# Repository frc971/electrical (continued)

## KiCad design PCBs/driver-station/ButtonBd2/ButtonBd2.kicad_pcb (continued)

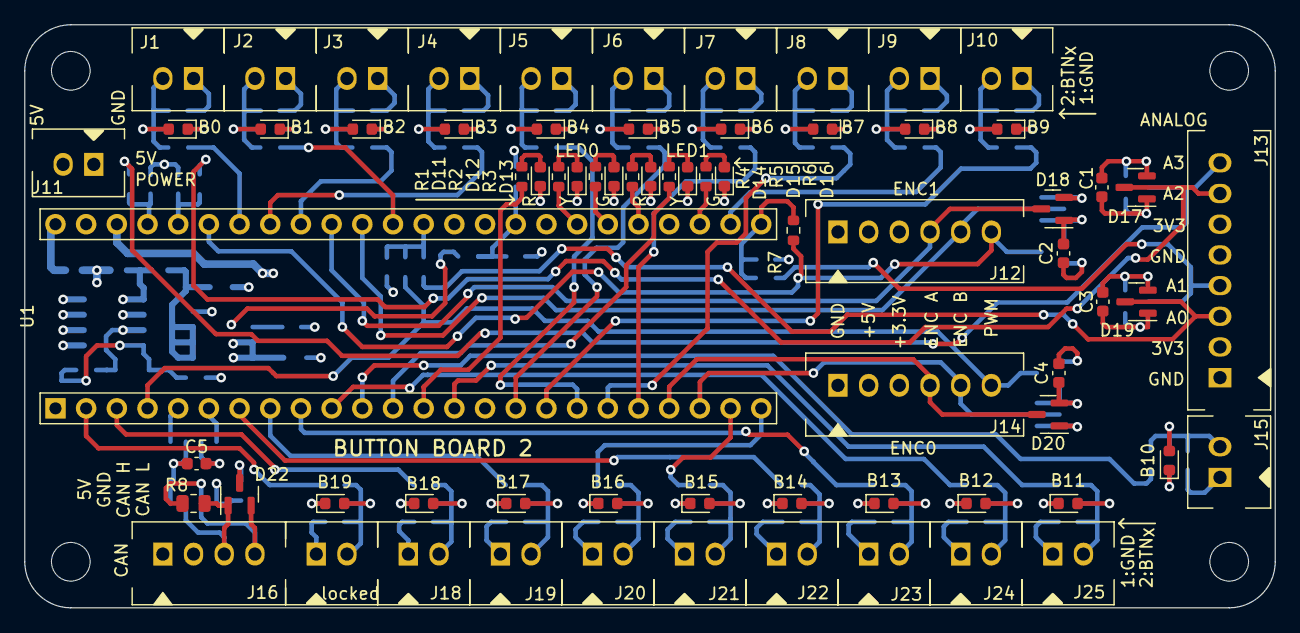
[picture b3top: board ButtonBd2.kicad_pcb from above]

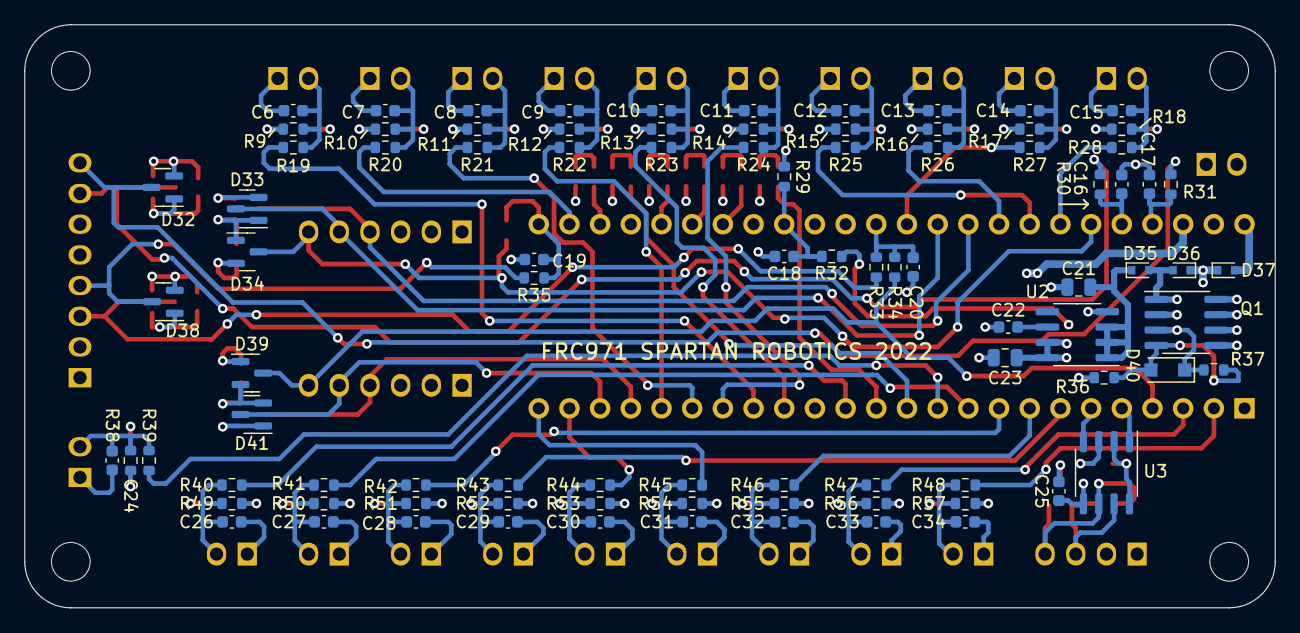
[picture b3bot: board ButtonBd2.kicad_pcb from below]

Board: 4 copper layers, 103.5 x 48.3 mm, 165 parts (91 on the bottom side), 100 nets.

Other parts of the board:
locked: B19; 70543-0001

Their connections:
/Button Inputs/BN19: locked.2; also elsewhere on the board
GND: locked.1; also elsewhere on the board

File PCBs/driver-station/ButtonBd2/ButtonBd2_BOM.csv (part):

Source:,/home/scott/Documents/Projects/FRC/ButtonBoard2/ButtonBd2/ButtonBd2.kicad_sch,,,,,,,
Date:,Sun 18 Dec 2022 03:10:28 PM PST,,,,,,,
Tool:,Eeschema 6.0.7-f9a2dced07~116~ubuntu20.04.1,,,,,,,
Generator:,/usr/share/kicad/plugins/bom_csv_grouped_by_value.py,,,,,,,
Component Count:,161,,,,,,,
,,,,,,,,
,,,,,,,,
Item,Qty,Reference(s),Value,LibPart,Footprint,Datasheet,MFG,MFG P/N
1,11,"C1, C2, C3, C4, C5, C16, C17, C18, C19, C20, C25",0.1uF-10%-50V-0603,Device:C,Capacitor_SMD:C_0603_1608Metric,~,Samsung Electro-Mechanics,CL10B104KB8NNNC
2,20,"C6, C7, C8, C9, C10, C11, C12, C13, C14, C15, C24, C26, C27, C28, C29, C30, C31, C32, C33, C34",1nF-50V-10%-0603,Device:C,Capacitor_SMD:C_0603_1608Metric,~,Samsung Electro-Mechanics,CL10B102KB8NNNC
3,1,C21,22uF-10V-10%-0805,Device:C,Capacitor_SMD:C_0805_2012Metric,~,Samsung Electro-Mechanics,CL21A226KPCLRNC
4,1,C22,3.3nF-50V-10%-0603,Device:C,Capacitor_SMD:C_0603_1608Metric,~,Samsung Electro-Mechanics,CL10B332KB8NNNC
5,1,C23,1uF-25V-10%-0805,Device:C,Capacitor_SMD:C_0805_2012Metric,~,Samsung Electro-Mechanics,CL21B105KAFNNNE
6,1,D1,BTN0,Device:LED,LED_SMD:LED_0603_1608Metric,https://www.we-online.com/katalog/datasheet/150060YS75000.pdf,Wurth Electronik,150060YS75000
7,1,D2,BTN1,Device:LED,LED_SMD:LED_0603_1608Metric,https://www.we-online.com/katalog/datasheet/150060YS75000.pdf,Wurth Electronik,150060YS75000
8,1,D3,BTN2,Device:LED,LED_SMD:LED_0603_1608Metric,https://www.we-online.com/katalog/datasheet/150060YS75000.pdf,Wurth Electronik,150060YS75000
9,1,D4,BTN3,Device:LED,LED_SMD:LED_0603_1608Metric,https://www.we-online.com/katalog/datasheet/150060YS75000.pdf,Wurth Electronik,150060YS75000
10,1,D5,BTN4,Device:LED,LED_SMD:LED_0603_1608Metric,https://www.we-online.com/katalog/datasheet/150060YS75000.pdf,Wurth Electronik,150060YS75000
11,1,D6,BTN5,Device:LED,LED_SMD:LED_0603_1608Metric,https://www.we-online.com/katalog/datasheet/150060YS75000.pdf,Wurth Electronik,150060YS75000
12,1,D7,BTN6,Device:LED,LED_SMD:LED_0603_1608Metric,https://www.we-online.com/katalog/datasheet/150060YS75000.pdf,Wurth Electronik,150060YS75000
13,1,D8,BTN7,Device:LED,LED_SMD:LED_0603_1608Metric,https://www.we-online.com/katalog/datasheet/150060YS75000.pdf,Wurth Electronik,150060YS75000
14,1,D9,BTN8,Device:LED,LED_SMD:LED_0603_1608Metric,https://www.we-online.com/katalog/datasheet/150060YS75000.pdf,Wurth Electronik,150060YS75000
15,1,D10,BTN9,Device:LED,LED_SMD:LED_0603_1608Metric,https://www.we-online.com/katalog/datasheet/150060YS75000.pdf,Wurth Electronik,150060YS75000
16,1,D11,0R,Device:LED,LED_SMD:LED_0603_1608Metric,http://www.stanley-components.com/php/downloaddatafile.php?r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,Stanley Electric,BR1111C-TR
17,1,D12,0Y,Device:LED,LED_SMD:LED_0603_1608Metric,https://www.we-online.com/katalog/datasheet/150060YS75000.pdf,Wurth Electronik,150060YS75000
18,1,D13,0G,Device:LED,LED_SMD:LED_0603_1608Metric,https://www.we-online.com/katalog/datasheet/150060YS75000.pdf,Wurth Electronik,150060GS75000
19,1,D14,1R,Device:LED,LED_SMD:LED_0603_1608Metric,http://www.stanley-components.com/php/downloaddatafile.php?r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,Stanley Electric,BR1111C-TR
20,1,D15,1Y,Device:LED,LED_SMD:LED_0603_1608Metric,https://www.we-online.com/katalog/datasheet/150060YS75000.pdf,Wurth Electronik,150060YS75000
21,1,D16,1G,Device:LED,LED_SMD:LED_0603_1608Metric,https://www.we-online.com/katalog/datasheet/150060YS75000.pdf,Wurth Electronik,150060GS75000
22,10,"D17, D18, D19, D20, D32, D33, D34, D38, D39, D41",BAV99,Diode:BAV99,Package_TO_SOT_SMD:SOT-23,https://assets.nexperia.com/documents/data-sheet/BAV99_SER.pdf,Nexperia USA Inc.,"BAV99,235"
23,1,D21,BTN10,Device:LED,LED_SMD:LED_0603_1608Metric,https://www.we-online.com/katalog/datasheet/150060YS75000.pdf,Wurth Electronik,150060YS75000
24,1,D22,PESD1CAN,PI-Power-Board:PESD1CAN,Package_TO_SOT_SMD:SOT-23,https://assets.nexperia.com/documents/data-sheet/PESD1CAN.pdf,Nexperia,"PESD1CAN,215"
25,1,D23,BTN19,Device:LED,LED_SMD:LED_0603_1608Metric,https://www.we-online.com/katalog/datasheet/150060YS75000.pdf,Wurth Electronik,150060YS75000
26,1,D24,BTN18,Device:LED,LED_SMD:LED_0603_1608Metric,https://www.we-online.com/katalog/datasheet/150060YS75000.pdf,Wurth Electronik,150060YS75000
27,1,D25,BTN17,Device:LED,LED_SMD:LED_0603_1608Metric,https://www.we-online.com/katalog/datasheet/150060YS75000.pdf,Wurth Electronik,150060YS75000
28,1,D26,BTN16,Device:LED,LED_SMD:LED_0603_1608Metric,https://www.we-online.com/katalog/datasheet/150060YS75000.pdf,Wurth Electronik,150060YS75000
29,1,D27,BTN15,Device:LED,LED_SMD:LED_0603_1608Metric,https://www.we-online.com/katalog/datasheet/150060YS75000.pdf,Wurth Electronik,150060YS75000
30,1,D28,BTN14,Device:LED,LED_SMD:LED_0603_1608Metric,https://www.we-online.com/katalog/datasheet/150060YS75000.pdf,Wurth Electronik,150060YS75000
31,1,D29,BTN13,Device:LED,LED_SMD:LED_0603_1608Metric,https://www.we-online.com/katalog/datasheet/150060YS75000.pdf,Wurth Electronik,150060YS75000
32,1,D30,BTN12,Device:LED,LED_SMD:LED_0603_1608Metric,https://www.we-online.com/katalog/datasheet/150060YS75000.pdf,Wurth Electronik,150060YS75000
33,1,D31,BTN11,Device:LED,LED_SMD:LED_0603_1608Metric,https://www.we-online.com/katalog/datasheet/150060YS75000.pdf,Wurth Electronik,150060YS75000
34,3,"D35, D36, D37",NSR05T40XV2T5G,Device:D_Schottky,Diode_SMD:D_SOD-523,~,onsemi,NSR05T40XV2T5G
35,1,D40,15V,Device:D_Zener,Diode_SMD:D_SOD-123F,~,Nexperia,"BZT52H-C15,115"
36,1,J1,B0,Connector:Conn_01x02_Male,ButtonBd2:70543-0001,https://www.molex.com/pdm_docs/sd/705430001_sd.pdf,Molex,70541-0001
37,1,J2,B1,Connector:Conn_01x02_Male,ButtonBd2:70543-0001,https://www.molex.com/pdm_docs/sd/705430001_sd.pdf,Molex,70541-0001
38,1,J3,B2,Connector:Conn_01x02_Male,ButtonBd2:70543-0001,https://www.molex.com/pdm_docs/sd/705430001_sd.pdf,Molex,70541-0001
39,1,J4,B3,Connector:Conn_01x02_Male,ButtonBd2:70543-0001,https://www.molex.com/pdm_docs/sd/705430001_sd.pdf,Molex,70541-0001
40,1,J5,B4,Connector:Conn_01x02_Male,ButtonBd2:70543-0001,https://www.molex.com/pdm_docs/sd/705430001_sd.pdf,Molex,70541-0001
41,1,J6,B5,Connector:Conn_01x02_Male,ButtonBd2:70543-0001,https://www.molex.com/pdm_docs/sd/705430001_sd.pdf,Molex,70541-0001
42,1,J7,B6,Connector:Conn_01x02_Male,ButtonBd2:70543-0001,https://www.molex.com/pdm_docs/sd/705430001_sd.pdf,Molex,70541-0001
43,1,J8,B7,Connector:Conn_01x02_Male,ButtonBd2:70543-0001,https://www.molex.com/pdm_docs/sd/705430001_sd.pdf,Molex,70541-0001
44,1,J9,B8,Connector:Conn_01x02_Male,ButtonBd2:70543-0001,https://www.molex.com/pdm_docs/sd/705430001_sd.pdf,Molex,70541-0001
45,1,J10,B9,Connector:Conn_01x02_Male,ButtonBd2:70543-0001,https://www.molex.com/pdm_docs/sd/705430001_sd.pdf,Molex,70541-0001
46,1,J11,POWER,Connector:Conn_01x02_Male,ButtonBd2:70543-0001,https://www.molex.com/pdm_docs/sd/705430001_sd.pdf,Molex,70541-0001
47,1,J12,ENC1,Connector:Conn_01x06_Male,ButtonBd2:70543-0005,https://www.molex.com/pdm_docs/sd/705430001_sd.pdf,Molex,70541-0005
48,1,J13,ANALOG,Connector:Conn_01x08_Male,ButtonBd2:70543-0007,https://www.molex.com/pdm_docs/sd/705430001_sd.pdf,Molex,70541-0007
49,1,J14,ENC0,Connector:Conn_01x06_Male,ButtonBd2:70543-0005,https://www.molex.com/pdm_docs/sd/705430001_sd.pdf,Molex,70541-0005
50,1,J15,B10,Connector:Conn_01x02_Male,ButtonBd2:70543-0001,https://www.molex.com/pdm_docs/sd/705430001_sd.pdf,Molex,70541-0001
51,1,J16,CAN,Connector:Conn_01x04_Male,ButtonBd2:70543-0003,https://www.molex.com/pdm_docs/sd/705430001_sd.pdf,Molex,70541-0003
52,1,J17,B19,Connector:Conn_01x02_Male,ButtonBd2:70543-0001,https://www.molex.com/pdm_docs/sd/705430001_sd.pdf,Molex,70541-0001
53,1,J18,B18,Connector:Conn_01x02_Male,ButtonBd2:70543-0001,https://www.molex.com/pdm_docs/sd/705430001_sd.pdf,Molex,70541-0001
54,1,J19,B17,Connector:Conn_01x02_Male,ButtonBd2:70543-0001,https://www.molex.com/pdm_docs/sd/705430001_sd.pdf,Molex,70541-0001
55,1,J20,B16,Connector:Conn_01x02_Male,ButtonBd2:70543-0001,https://www.molex.com/pdm_docs/sd/705430001_sd.pdf,Molex,70541-0001
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
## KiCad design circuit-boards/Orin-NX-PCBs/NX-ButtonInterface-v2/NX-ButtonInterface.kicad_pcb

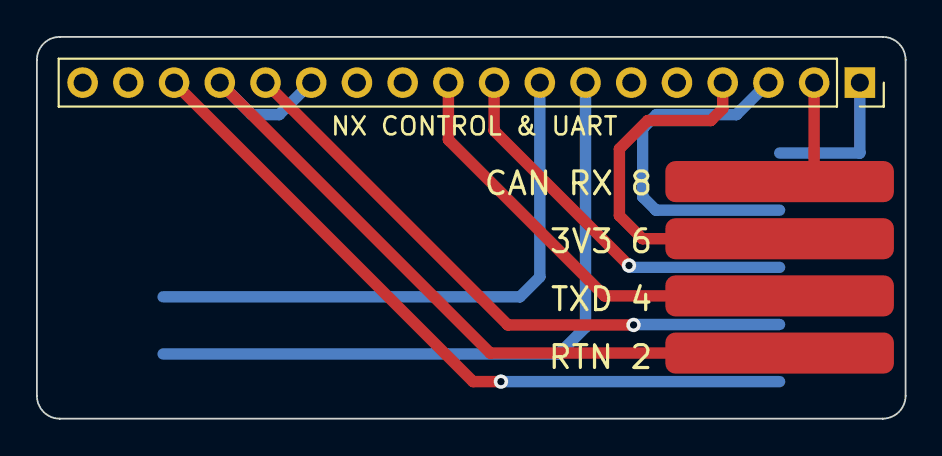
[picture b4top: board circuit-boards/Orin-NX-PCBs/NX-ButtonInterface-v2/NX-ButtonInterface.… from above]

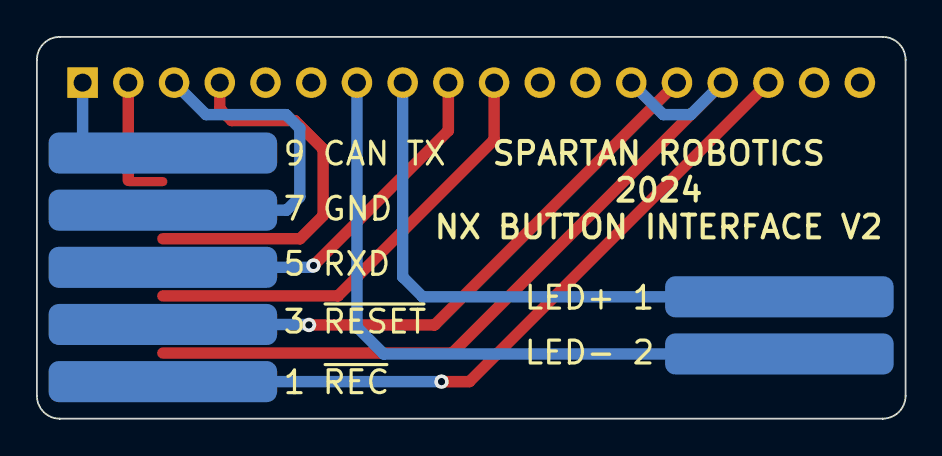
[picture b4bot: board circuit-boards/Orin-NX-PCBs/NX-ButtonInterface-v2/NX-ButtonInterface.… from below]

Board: 2 copper layers, 48.3 x 21.2 mm, 3 parts (2 on the bottom side), 11 nets.

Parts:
J1: NX CONTROL & UART; PinSocket_1x18_P2.54mm_Vertical
J2: NX-BUTTON; 9-pin-solder-pads
J4: POWER LED; 2-pin-solder-pads

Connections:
/3V3: J1.4, J2.6
/CAN_RX: J1.2, J2.8
/CAN_TX: J1.1, J2.9
/GND: J1.3, J2.7
/NX_PC_LED+: J1.8, J4.1
/NX_PC_LED-: J1.7, J4.2
/SYS_RST_RCV_RTN: J1.13, J1.15, J2.2
/UART2_RXD: J1.9, J2.5
/UART2_TXD: J1.10, J2.4
/~REC: J1.16, J2.1
/~SYS_RESET: J1.14, J2.3

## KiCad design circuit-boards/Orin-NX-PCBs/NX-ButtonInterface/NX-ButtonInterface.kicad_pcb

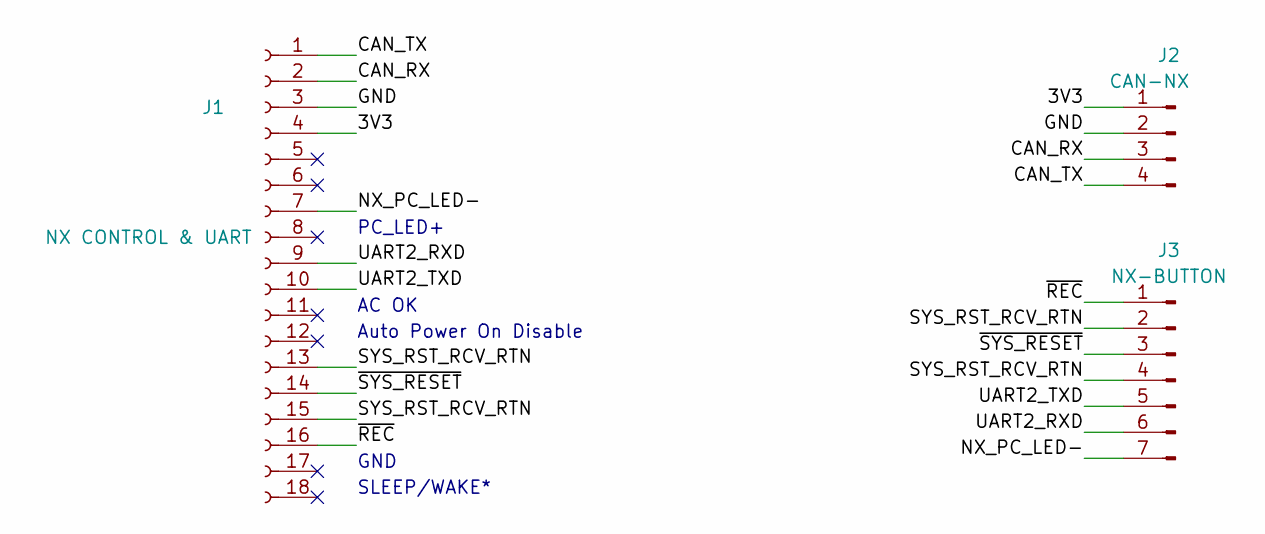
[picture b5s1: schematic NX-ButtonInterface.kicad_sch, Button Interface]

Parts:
J1: NX CONTROL & UART; PinSocket_1x18_P2.54mm_Vertical; MFG P/N PPTC181LFBN-RC
J2: CAN-NX; 4-pin-solder-pads
J3: NX-BUTTON; 7-pin-solder-pads

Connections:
/3V3: J1.4, J2.1
/CAN_RX: J1.2, J2.3
/CAN_TX: J1.1, J2.4
/GND: J1.3, J2.2
/NX_PC_LED-: J1.7, J3.7
/SYS_RST_RCV_RTN: J1.13, J1.15, J3.2, J3.4
/UART2_RXD: J1.9, J3.6
/UART2_TXD: J1.10, J3.5
/~REC: J1.16, J3.1
/~SYS_RESET: J1.14, J3.3

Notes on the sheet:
AC OK
GND
PC_LED+
Auto Power On Disable
SLEEP/WAKE*

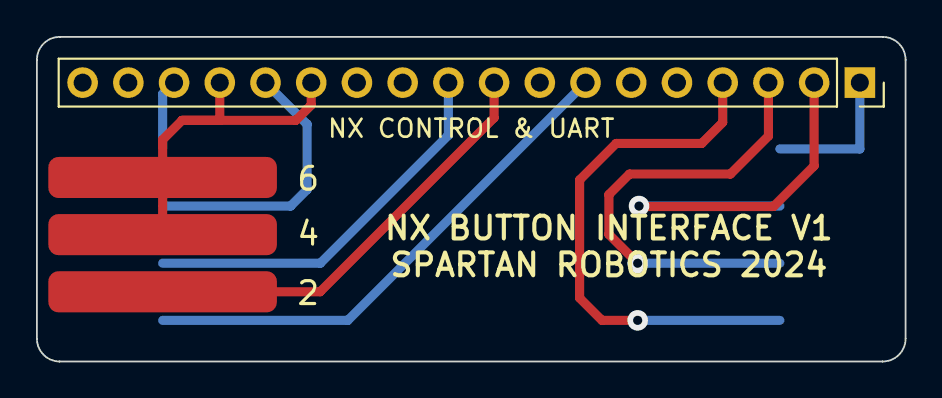
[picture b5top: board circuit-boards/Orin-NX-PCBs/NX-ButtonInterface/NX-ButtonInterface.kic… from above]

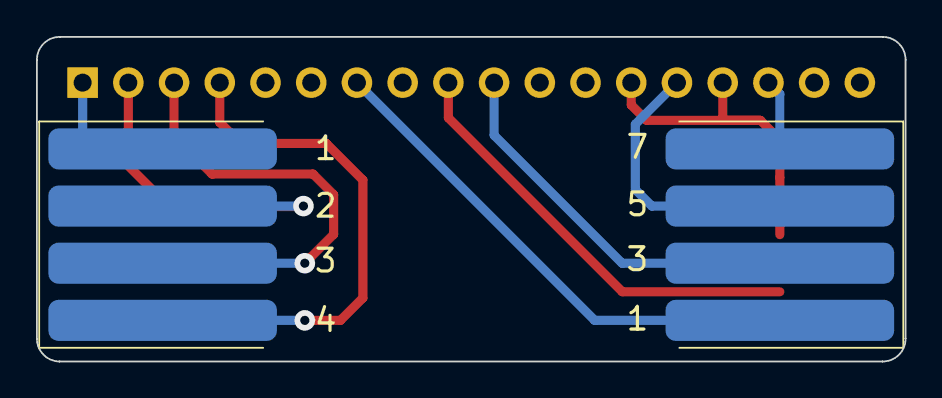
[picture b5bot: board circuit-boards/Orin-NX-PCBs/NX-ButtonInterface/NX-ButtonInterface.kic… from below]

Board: 2 copper layers, 48.3 x 18.0 mm, 3 parts (2 on the bottom side), 10 nets.

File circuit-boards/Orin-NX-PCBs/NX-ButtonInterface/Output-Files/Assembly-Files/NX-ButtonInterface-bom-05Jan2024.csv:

Item, Qty, Reference(s), Value, DIST, DIST P/N, MFG, MFG P/N, 
"1","1","J1","NX CONTROL & UART","Digikey","S7016-ND","Sullins Connector Solutions","PPTC181LFBN-RC"
"2","1","J2","CAN-NX","Digikey","WM4802-ND","Molex","0705430003"
"3","1","J3","NX-BUTTON","Digikey","WM4805-ND","Molex","0705430006"

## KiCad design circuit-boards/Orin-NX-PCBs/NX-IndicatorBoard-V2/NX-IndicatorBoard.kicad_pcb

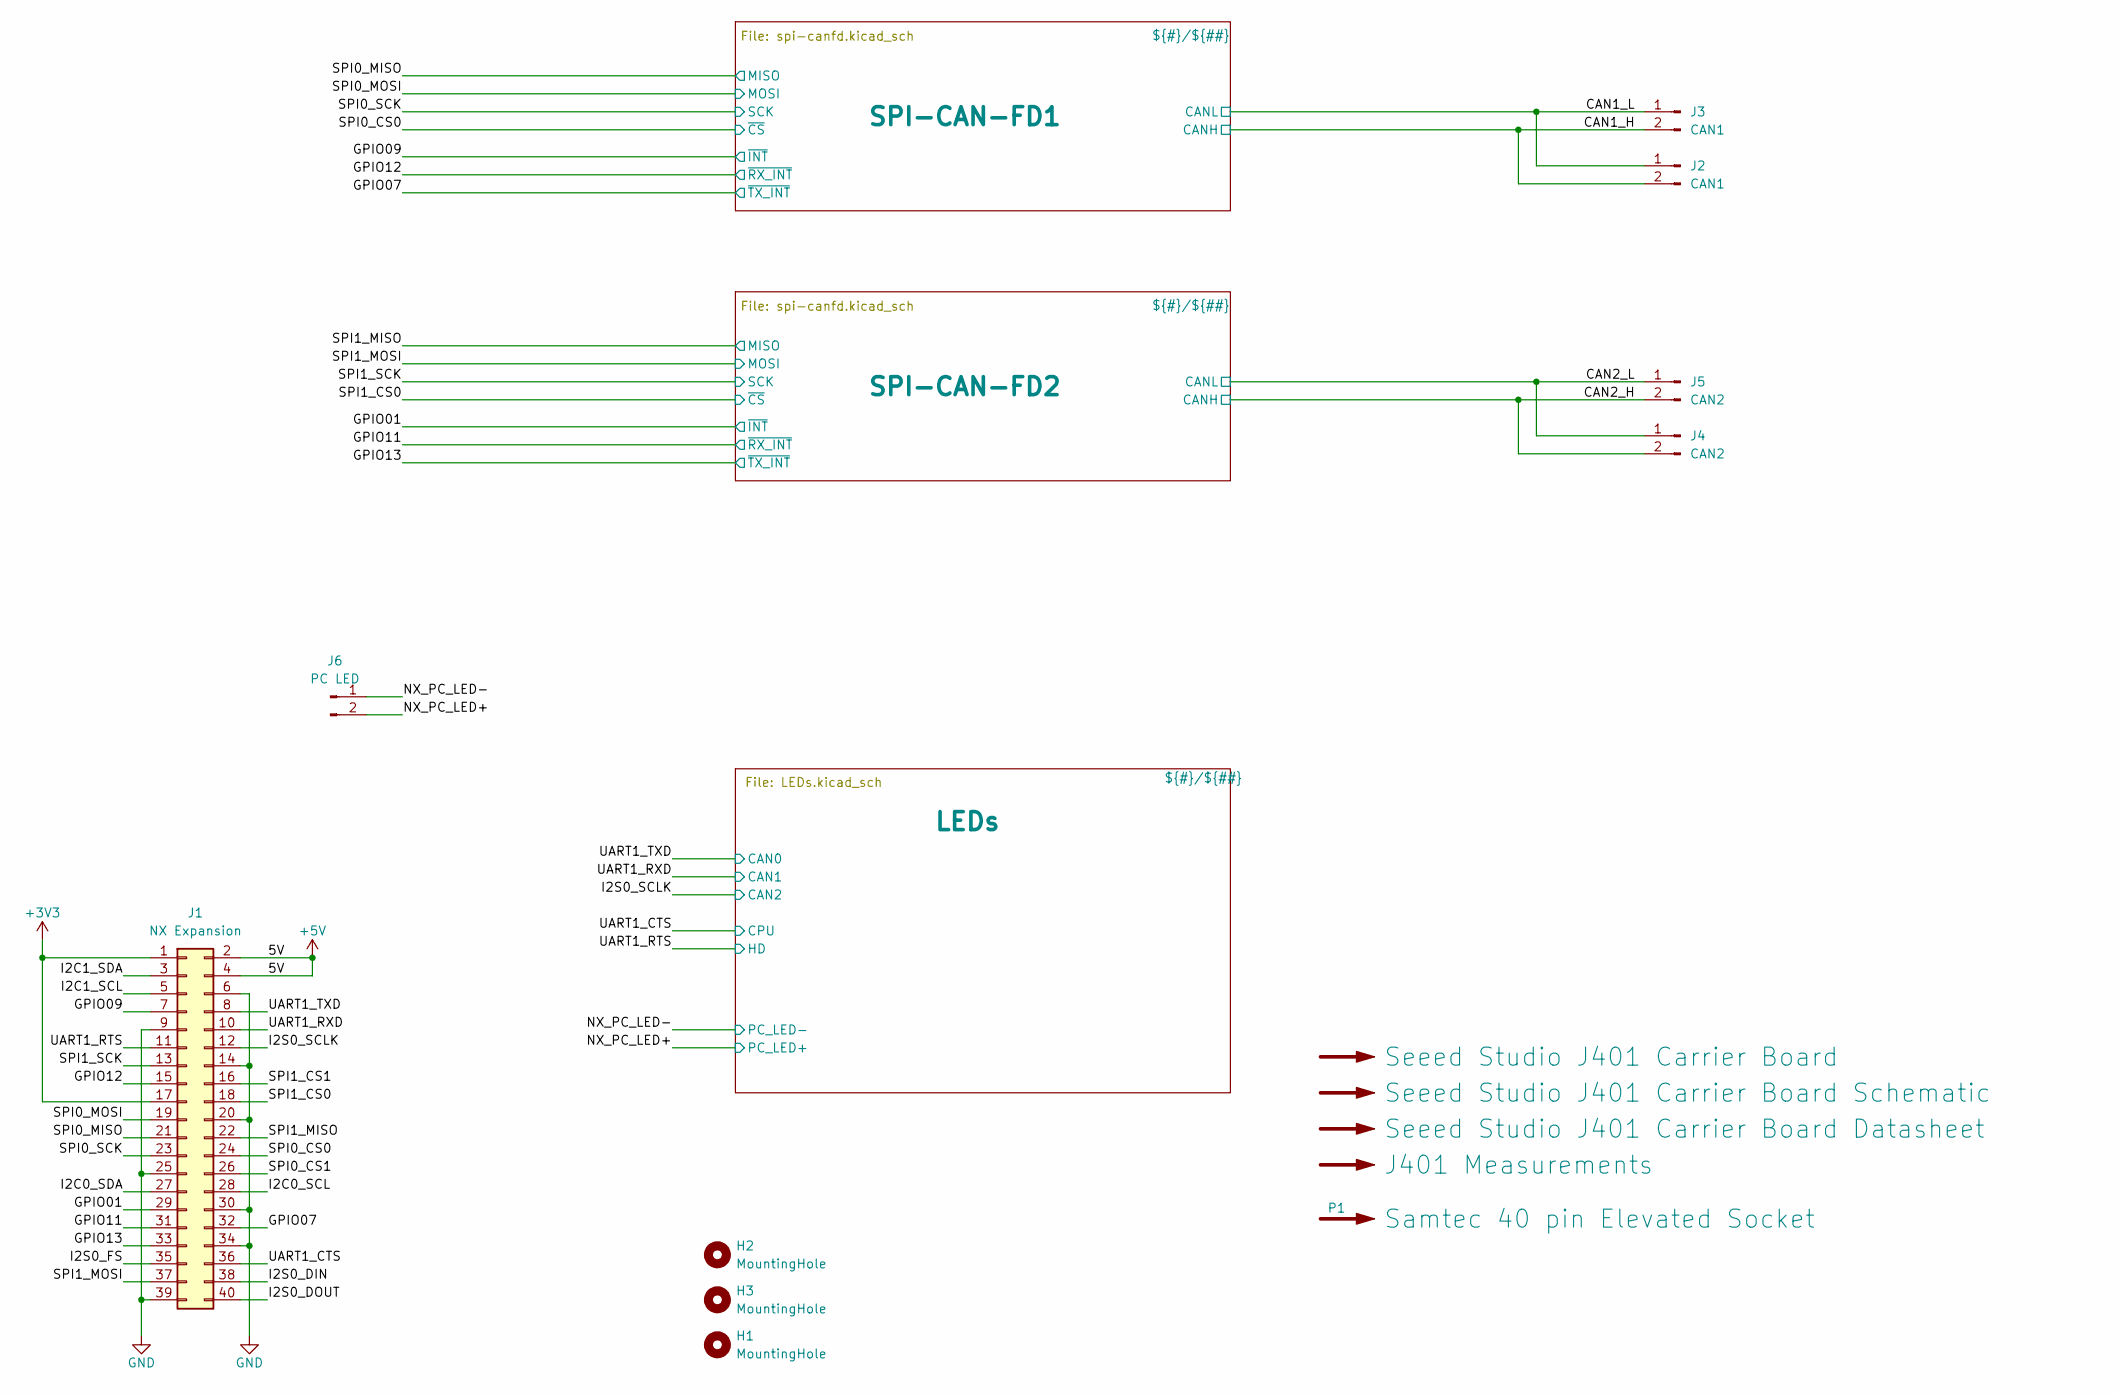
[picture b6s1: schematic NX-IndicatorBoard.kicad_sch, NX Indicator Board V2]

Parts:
H1, H2, H3: MountingHole; MountingHole_2.7mm_M2.5_Pad
J1: NX Expansion; M20-782045; MFG P/N M20-7812045
J2, J3: CAN1; 70555-0001; MFG P/N 0705550036
J4, J5: CAN2; 70555-0001; MFG P/N 0705550036
J6: PC LED; 70543-0001; MFG P/N 0705430036
P1: Samtec 40 pin Elevated Socket; MFG P/N ESQ-120-34-G-D

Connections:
+3V3: J1.1, J1.17; also elsewhere on the board
+5V: J1.2, J1.4; also elsewhere on the board
/CAN1_H: J2.2, J3.2; also elsewhere on the board
/CAN1_L: J2.1, J3.1; also elsewhere on the board
/CAN2_H: J4.2, J5.2; also elsewhere on the board
/CAN2_L: J4.1, J5.1; also elsewhere on the board
/GPIO01: J1.29; also elsewhere on the board
/GPIO07: J1.32; also elsewhere on the board
/GPIO09: J1.7; also elsewhere on the board
/GPIO11: J1.31; also elsewhere on the board
/GPIO12: J1.15; also elsewhere on the board
/GPIO13: J1.33; also elsewhere on the board
/I2C0_SCL: J1.28
/I2C0_SDA: J1.27
/I2C1_SCL: J1.5
/I2C1_SDA: J1.3
/I2S0_DIN: J1.38
/I2S0_DOUT: J1.40
/I2S0_FS: J1.35
/I2S0_SCLK: J1.12; also elsewhere on the board
/NX_PC_LED+: J6.2; also elsewhere on the board
/NX_PC_LED-: J6.1; also elsewhere on the board
/SPI0_CS0: J1.24; also elsewhere on the board
/SPI0_CS1: J1.26
/SPI0_MISO: J1.21; also elsewhere on the board
/SPI0_MOSI: J1.19; also elsewhere on the board
/SPI0_SCK: J1.23; also elsewhere on the board
/SPI1_CS0: J1.18; also elsewhere on the board
/SPI1_CS1: J1.16
/SPI1_MISO: J1.22; also elsewhere on the board
/SPI1_MOSI: J1.37; also elsewhere on the board
/SPI1_SCK: J1.13; also elsewhere on the board
/UART1_CTS: J1.36; also elsewhere on the board
/UART1_RTS: J1.11; also elsewhere on the board
/UART1_RXD: J1.10; also elsewhere on the board
/UART1_TXD: J1.8; also elsewhere on the board
GND: J1.6, J1.9, J1.14, J1.20, J1.25, J1.30, J1.34, J1.39; also elsewhere on the board

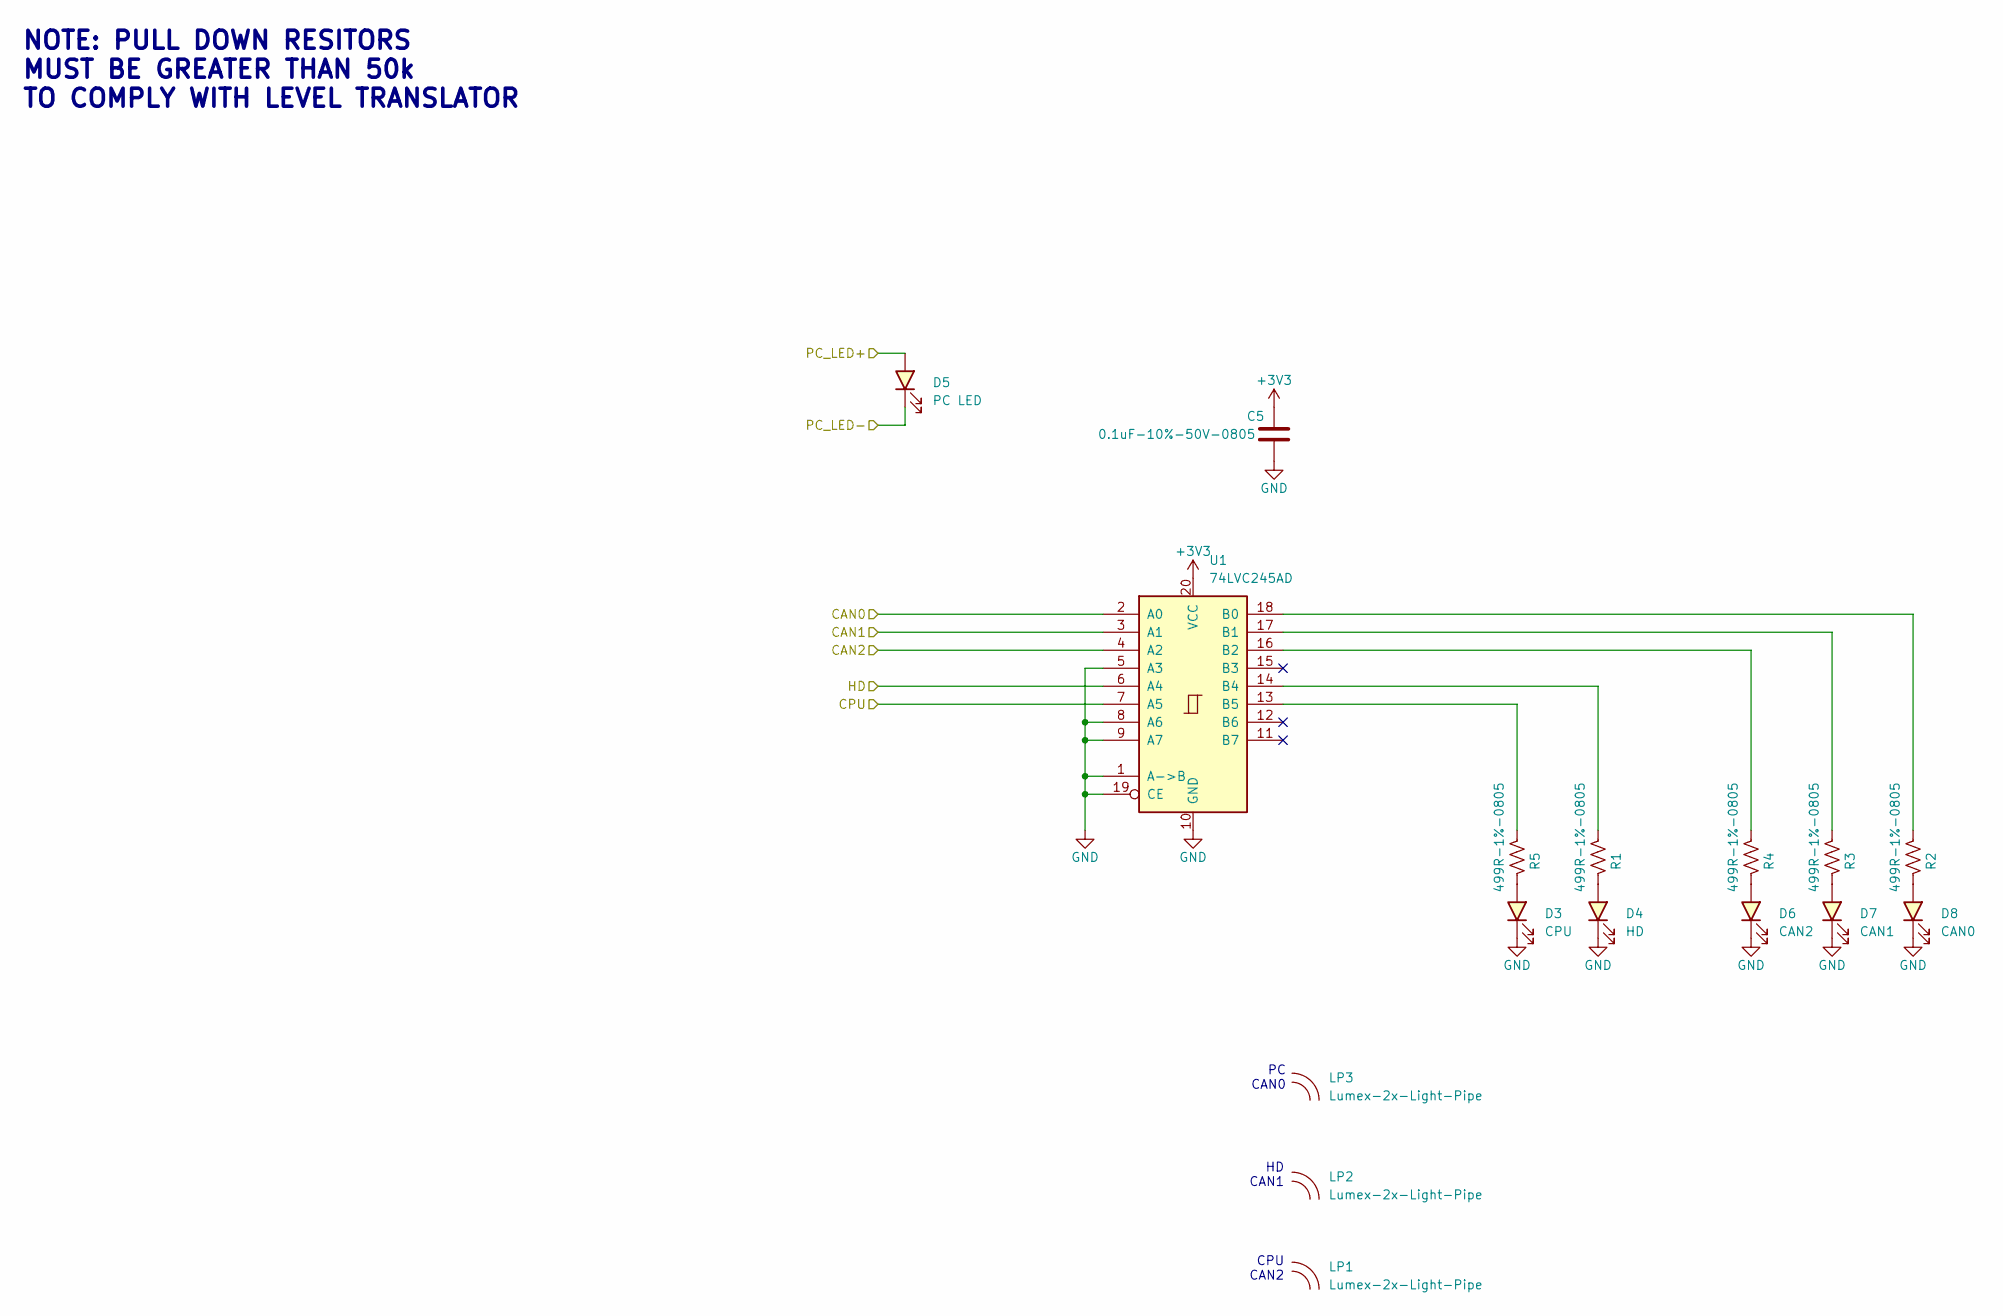
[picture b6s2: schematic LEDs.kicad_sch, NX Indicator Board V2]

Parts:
C5: 0.1uF-10%-50V-0805; C_0805_2012Metric; MFG P/N CC0805KRX7R9BB104
D3: CPU; LED_1206_3216Metric; MFG P/N QTLP650D4TR
D4: HD; LED_1206_3216Metric; MFG P/N QTLP650D4TR
D5: PC LED; LED_1206_3216Metric; MFG P/N QTLP650D4TR
D6: CAN2; LED_1206_3216Metric; MFG P/N QTLP650D4TR
D7: CAN1; LED_1206_3216Metric; MFG P/N QTLP650D4TR
D8: CAN0; LED_1206_3216Metric; MFG P/N QTLP650D4TR
LP1, LP2, LP3: Lumex-2x-Light-Pipe; Lumex-LPF-C012303S; MFG P/N LPF-C012303S
R1, R2, R3, R4, R5: 499R-1%-0805; R_0805_2012Metric; MFG P/N RC0805FR-07499RL
U1: 74LVC245AD; SO-20_12.8x7.5mm_P1.27mm; MFG P/N 74LVC245AD,118

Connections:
+3V3: C5.1, U1.20 (VCC); also elsewhere on the board
/I2S0_SCLK: U1.4 (A2); also elsewhere on the board
/NX_PC_LED+: D5.2 (A); also elsewhere on the board
/NX_PC_LED-: D5.1 (K); also elsewhere on the board
/UART1_CTS: U1.7 (A5); also elsewhere on the board
/UART1_RTS: U1.6 (A4); also elsewhere on the board
/UART1_RXD: U1.3 (A1); also elsewhere on the board
/UART1_TXD: U1.2 (A0); also elsewhere on the board
GND: C5.2, D3.1 (K), D4.1 (K), D6.1 (K), D7.1 (K), D8.1 (K), U1.1 (A->B), U1.5 (A3), U1.8 (A6), U1.9 (A7), U1.10 (GND), U1.19 (CE); also elsewhere on the board
unnamed: D3.2 (A), R5.1
unnamed: D4.2 (A), R1.1
unnamed: D6.2 (A), R4.1
unnamed: D7.2 (A), R3.1
unnamed: D8.2 (A), R2.1
unnamed: R2.2, U1.18 (B0)
unnamed: R3.2, U1.17 (B1)
unnamed: R4.2, U1.16 (B2)
unnamed: R1.2, U1.14 (B4)
unnamed: R5.2, U1.13 (B5)

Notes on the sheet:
CPU CAN2
PC CAN0
HD CAN1
NOTE: PULL DOWN RESITORS MUST BE GREATER THAN 50k TO COMPLY WITH LEVEL TRANSLATOR

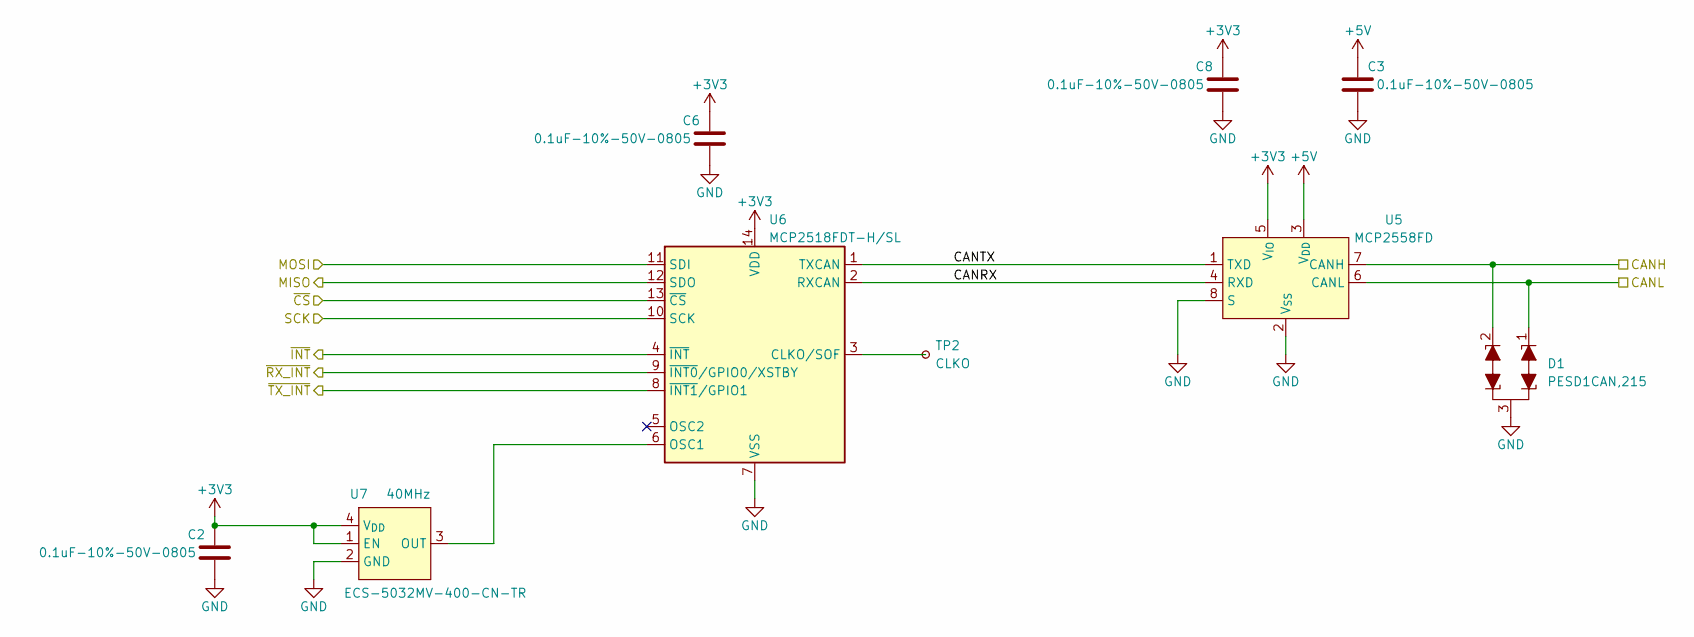
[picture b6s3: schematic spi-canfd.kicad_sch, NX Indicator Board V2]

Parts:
C2, C3, C6, C8: 0.1uF-10%-50V-0805; C_0805_2012Metric; MFG P/N CC0805KRX7R9BB104
D1: PESD1CAN; SOT-23; MFG P/N PESD1CAN,215
TP2: CLKO; TestPoint_THTPad_D1.0mm_Drill0.5mm
U5: MCP2558FD; SO-8_3.9x4.9mm_P1.27mm; MFG P/N MCP2558FD-H/SN
U6: MCP2518FDT-H/SL; SO-14_3.9x8.65mm_P1.27mm; MFG P/N MCP2518FDT-H/SL
U7: 40MHz; ECS-5032MV; MFG P/N ECS-5032MV-400-CN-TR

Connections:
+3V3: C2.1, C6.1, C8.1, U5.5 (V_{IO}), U6.14 (VDD), U7.1 (EN), U7.4 (V_{DD}); also elsewhere on the board
+5V: C3.1, U5.3 (V_{DD}); also elsewhere on the board
/CAN2_H: D1.2 (K1), U5.7 (CANH); also elsewhere on the board
/CAN2_L: D1.1 (K1), U5.6 (CANL); also elsewhere on the board
/GPIO01: U6.4 (~INT); also elsewhere on the board
/GPIO11: U6.9 (~INT0/GPIO0/XSTBY); also elsewhere on the board
/GPIO13: U6.8 (~INT1/GPIO1); also elsewhere on the board
/SPI1_CS0: U6.13 (~CS); also elsewhere on the board
/SPI1_MISO: U6.12 (SDO); also elsewhere on the board
/SPI1_MOSI: U6.11 (SDI); also elsewhere on the board
/SPI1_SCK: U6.10 (SCK); also elsewhere on the board
/SPI-CAN-FD2/CANRX: U5.4 (RXD), U6.2 (RXCAN)
/SPI-CAN-FD2/CANTX: U5.1 (TXD), U6.1 (TXCAN)
GND: C2.2, C3.2, C6.2, C8.2, D1.3 (KK), U5.2 (V_{SS}), U5.8 (S), U6.7 (VSS), U7.2 (GND); also elsewhere on the board
unnamed: TP2.1, U6.3 (CLKO/SOF)
unnamed: U6.6 (OSC1), U7.3 (OUT)

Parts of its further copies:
C1, C4, C7, C9: 0.1uF-10%-50V-0805; C_0805_2012Metric; MFG P/N CC0805KRX7R9BB104
D2: PESD1CAN; SOT-23; MFG P/N PESD1CAN,215
TP1: CLKO; TestPoint_THTPad_D1.0mm_Drill0.5mm
U2: MCP2558FD; SO-8_3.9x4.9mm_P1.27mm; MFG P/N MCP2558FD-H/SN
U3: MCP2518FDT-H/SL; SO-14_3.9x8.65mm_P1.27mm; MFG P/N MCP2518FDT-H/SL
U4: 40MHz; ECS-5032MV; MFG P/N ECS-5032MV-400-CN-TR

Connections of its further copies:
+3V3: C1.1, C7.1, C9.1, U2.5 (V_{IO}), U3.14 (VDD), U4.1 (EN), U4.4 (V_{DD}); also elsewhere on the board
+5V: C4.1, U2.3 (V_{DD}); also elsewhere on the board
/CAN1_H: D2.2 (K1), U2.7 (CANH); also elsewhere on the board
/CAN1_L: D2.1 (K1), U2.6 (CANL); also elsewhere on the board
/GPIO07: U3.8 (~INT1/GPIO1); also elsewhere on the board
/GPIO09: U3.4 (~INT); also elsewhere on the board
/GPIO12: U3.9 (~INT0/GPIO0/XSTBY); also elsewhere on the board
/SPI0_CS0: U3.13 (~CS); also elsewhere on the board
/SPI0_MISO: U3.12 (SDO); also elsewhere on the board
/SPI0_MOSI: U3.11 (SDI); also elsewhere on the board
/SPI0_SCK: U3.10 (SCK); also elsewhere on the board
/SPI-CAN-FD1/CANRX: U2.4 (RXD), U3.2 (RXCAN)
/SPI-CAN-FD1/CANTX: U2.1 (TXD), U3.1 (TXCAN)
GND: C1.2, C4.2, C7.2, C9.2, D2.3 (KK), U2.2 (V_{SS}), U2.8 (S), U3.7 (VSS), U4.2 (GND); also elsewhere on the board
unnamed: TP1.1, U3.3 (CLKO/SOF)
unnamed: U3.6 (OSC1), U4.3 (OUT)
